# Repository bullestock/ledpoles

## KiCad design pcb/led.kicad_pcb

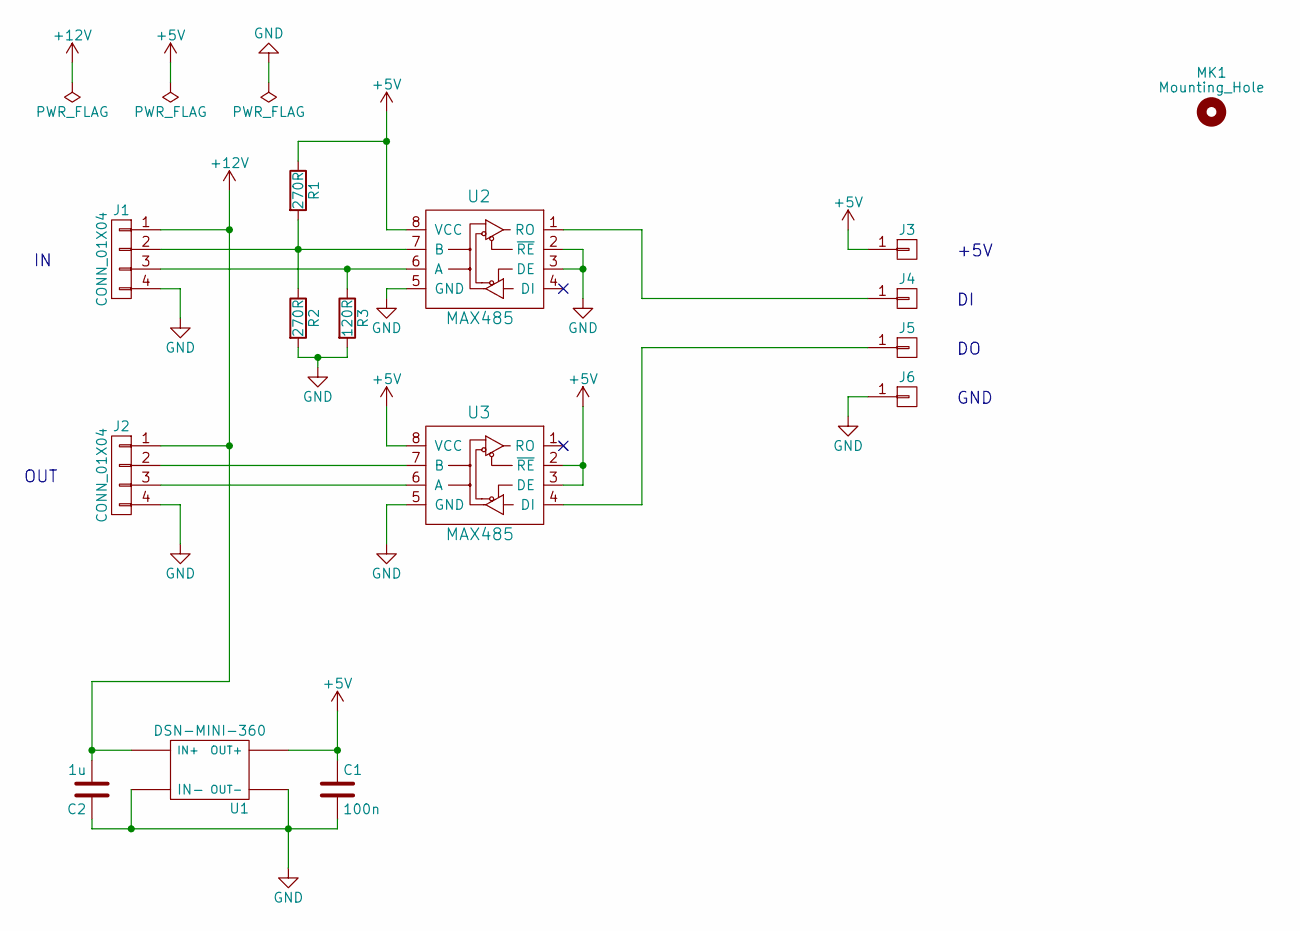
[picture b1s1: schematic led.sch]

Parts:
C1: 100n; C_0603
C2: 1u; C_0805
J1, J2: CONN_01X04; PhoenixContact_MC-G_04x3.50mm_Angled
J3, J4, J5, J6: CONN_01X01; SolderWirePad_single_1-2mmDrill
MK1: Mounting_Hole; MountingHole_3.5mm
R1, R2: 270R; R_0603
R3: 120R; R_0603
U1: DSN-MINI-360
U2, U3: MAX485; SOIC-8_3.9x4.9mm_Pitch1.27mm

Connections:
+5V: C1.1, J3.1, R1.1, U1.OUT+, U2.8 (VCC), U3.2 (~RE), U3.3 (DE), U3.8 (VCC)
+12V: C2.2, J1.1, J2.1, U1.IN+
GND: C1.2, C2.1, J1.4, J2.4, J6.1, R2.2, R3.2, U1.IN-, U1.OUT-, U2.2 (~RE), U2.3 (DE), U2.5 (GND), U3.5 (GND)
unnamed: J1.2, R1.2, R2.1, U2.7 (B)
unnamed: J1.3, R3.1, U2.6 (A)
unnamed: J2.2, U3.7 (B)
unnamed: J2.3, U3.6 (A)
unnamed: J4.1, U2.1 (RO)
unnamed: J5.1, U3.4 (DI)

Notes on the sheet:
OUT
GND
+5V

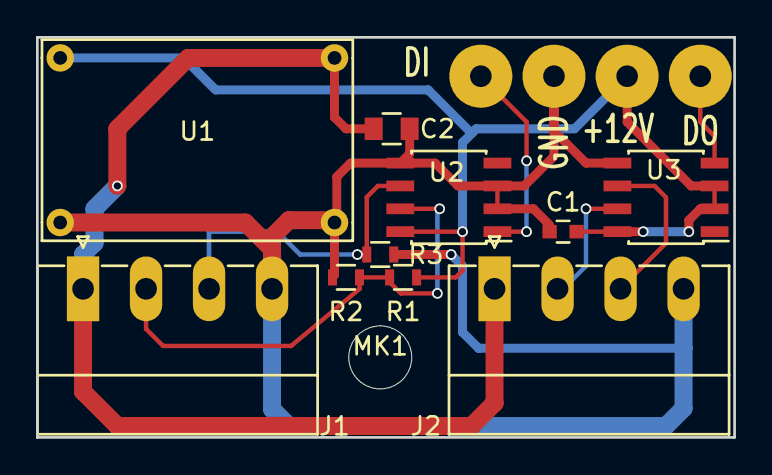
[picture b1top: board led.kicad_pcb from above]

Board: 2 copper layers, 38.7 x 22.2 mm, 15 parts (0 on the bottom side), 9 nets.

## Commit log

2017-03-20 Initial PCB
2017-04-02 Use relative paths.
2017-04-02 Adapt for optional 1-wire operation.
2017-04-02 Add measurements; update schematic.
2017-04-02 Use local libraries.
2017-04-02 Fix errors.
2017-04-07 Change to 3.5 mm pitch connectors. Finalize PCB layout.
2017-04-12 Adjust layout.
2017-05-22 Fix label.
2017-06-25 Add ESP code.
2017-06-25 Rename.
2017-06-25 Convert to FastLED and port Chairbot animations.
2017-06-26 Make non-autonomous mode work.
2017-06-26 Add Python test script.
2017-06-26 Add more patterns.
2017-06-26 Add command to set mode.
2017-06-26 Script to set autonomous mode.
2017-07-15 Fade between mode switch.
2017-07-15 Add strip modes.
2017-07-16 Fix strip mode switch bug.
2017-07-16 Use dynamic memory allocation. Prepare for 2 strands of LEDs.
2017-07-16 Add control box case.
2017-07-16 Fix bugs; mix order of animations.
2017-07-19 Set strip mode.
2017-07-19 Fix magic values.
2017-07-19 Fix byte order.
2017-07-19 Add speed control; let modes start at zero.
2017-07-22 Fix strip mode bug; add status LED.
2017-07-24 Fix mirroring bug; disable FastLED interrupts.
2017-07-26 Ready for deployment.
2017-07-27 Add Vammen SSID.
2017-07-30 Set station mode.
2017-07-30 Start responsiveness refactoring.
2017-07-30 Fix various issues.
2017-07-30 PoC.
2017-07-30 Add one more animation, tweak framework.
2017-07-30 More animations.
2017-07-30 But wait, there's more!
2017-07-30 You won't believe what happens in the next animation!
2017-07-30 Update UDP code.
2017-07-30 Tweak stuff.
2017-07-30 Documentation.
2017-07-30 Use case-insensitive compare.
2017-07-30 Disable.
2017-07-30 Increase speed.
2017-07-30 Clear when changing modes.
2017-07-30 Fix strand swapping bug.
2017-07-30 Cleanup.
2017-07-30 Use moar LEDs.
2017-07-30 Fix raw data bug.
2017-07-30 Ensure max brightness in non-autonomous mode.
2017-08-03 Make mDNS work.
2017-08-04 Use mDNS.
2017-08-21 Add optional address argument.
2017-08-24 Add brightness, night mode commands.
2017-08-25 Add offset.
2018-03-29 Set freerun mode.
2018-03-30 Use I2S (only supports one strand).
2018-03-30 Fix RGB/GRB issue.
2018-03-31 For ØU use.
2018-03-31 Fix RGB -> GRB conversion bug.
2018-03-31 Add visual connection signal.
2018-04-28 Start ESP32 port.
2018-04-28 Fix speed.
2018-04-30 Add OLED display.
2018-04-30 Eliminate status LED.
2018-05-01 Fix help text.
2018-05-05 Show RSSI on display.
2018-05-07 Show IP on startup.
2018-05-07 Show RSSI and uptime every five seconds.
2018-05-10 Replace LED with display; add antenna hole.
2018-08-22 Show number of poles on boot.
2018-08-23 Initial code for sign.
2020-08-26 update to be python3 compatible
2020-08-26 made script executable
